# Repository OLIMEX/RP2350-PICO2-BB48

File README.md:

# RP2350-PICO2-BB48
Raspberry Pi RP2350 PICO2 board with all 48 ports exposed, PSRAM 8MB, Flash 16MB

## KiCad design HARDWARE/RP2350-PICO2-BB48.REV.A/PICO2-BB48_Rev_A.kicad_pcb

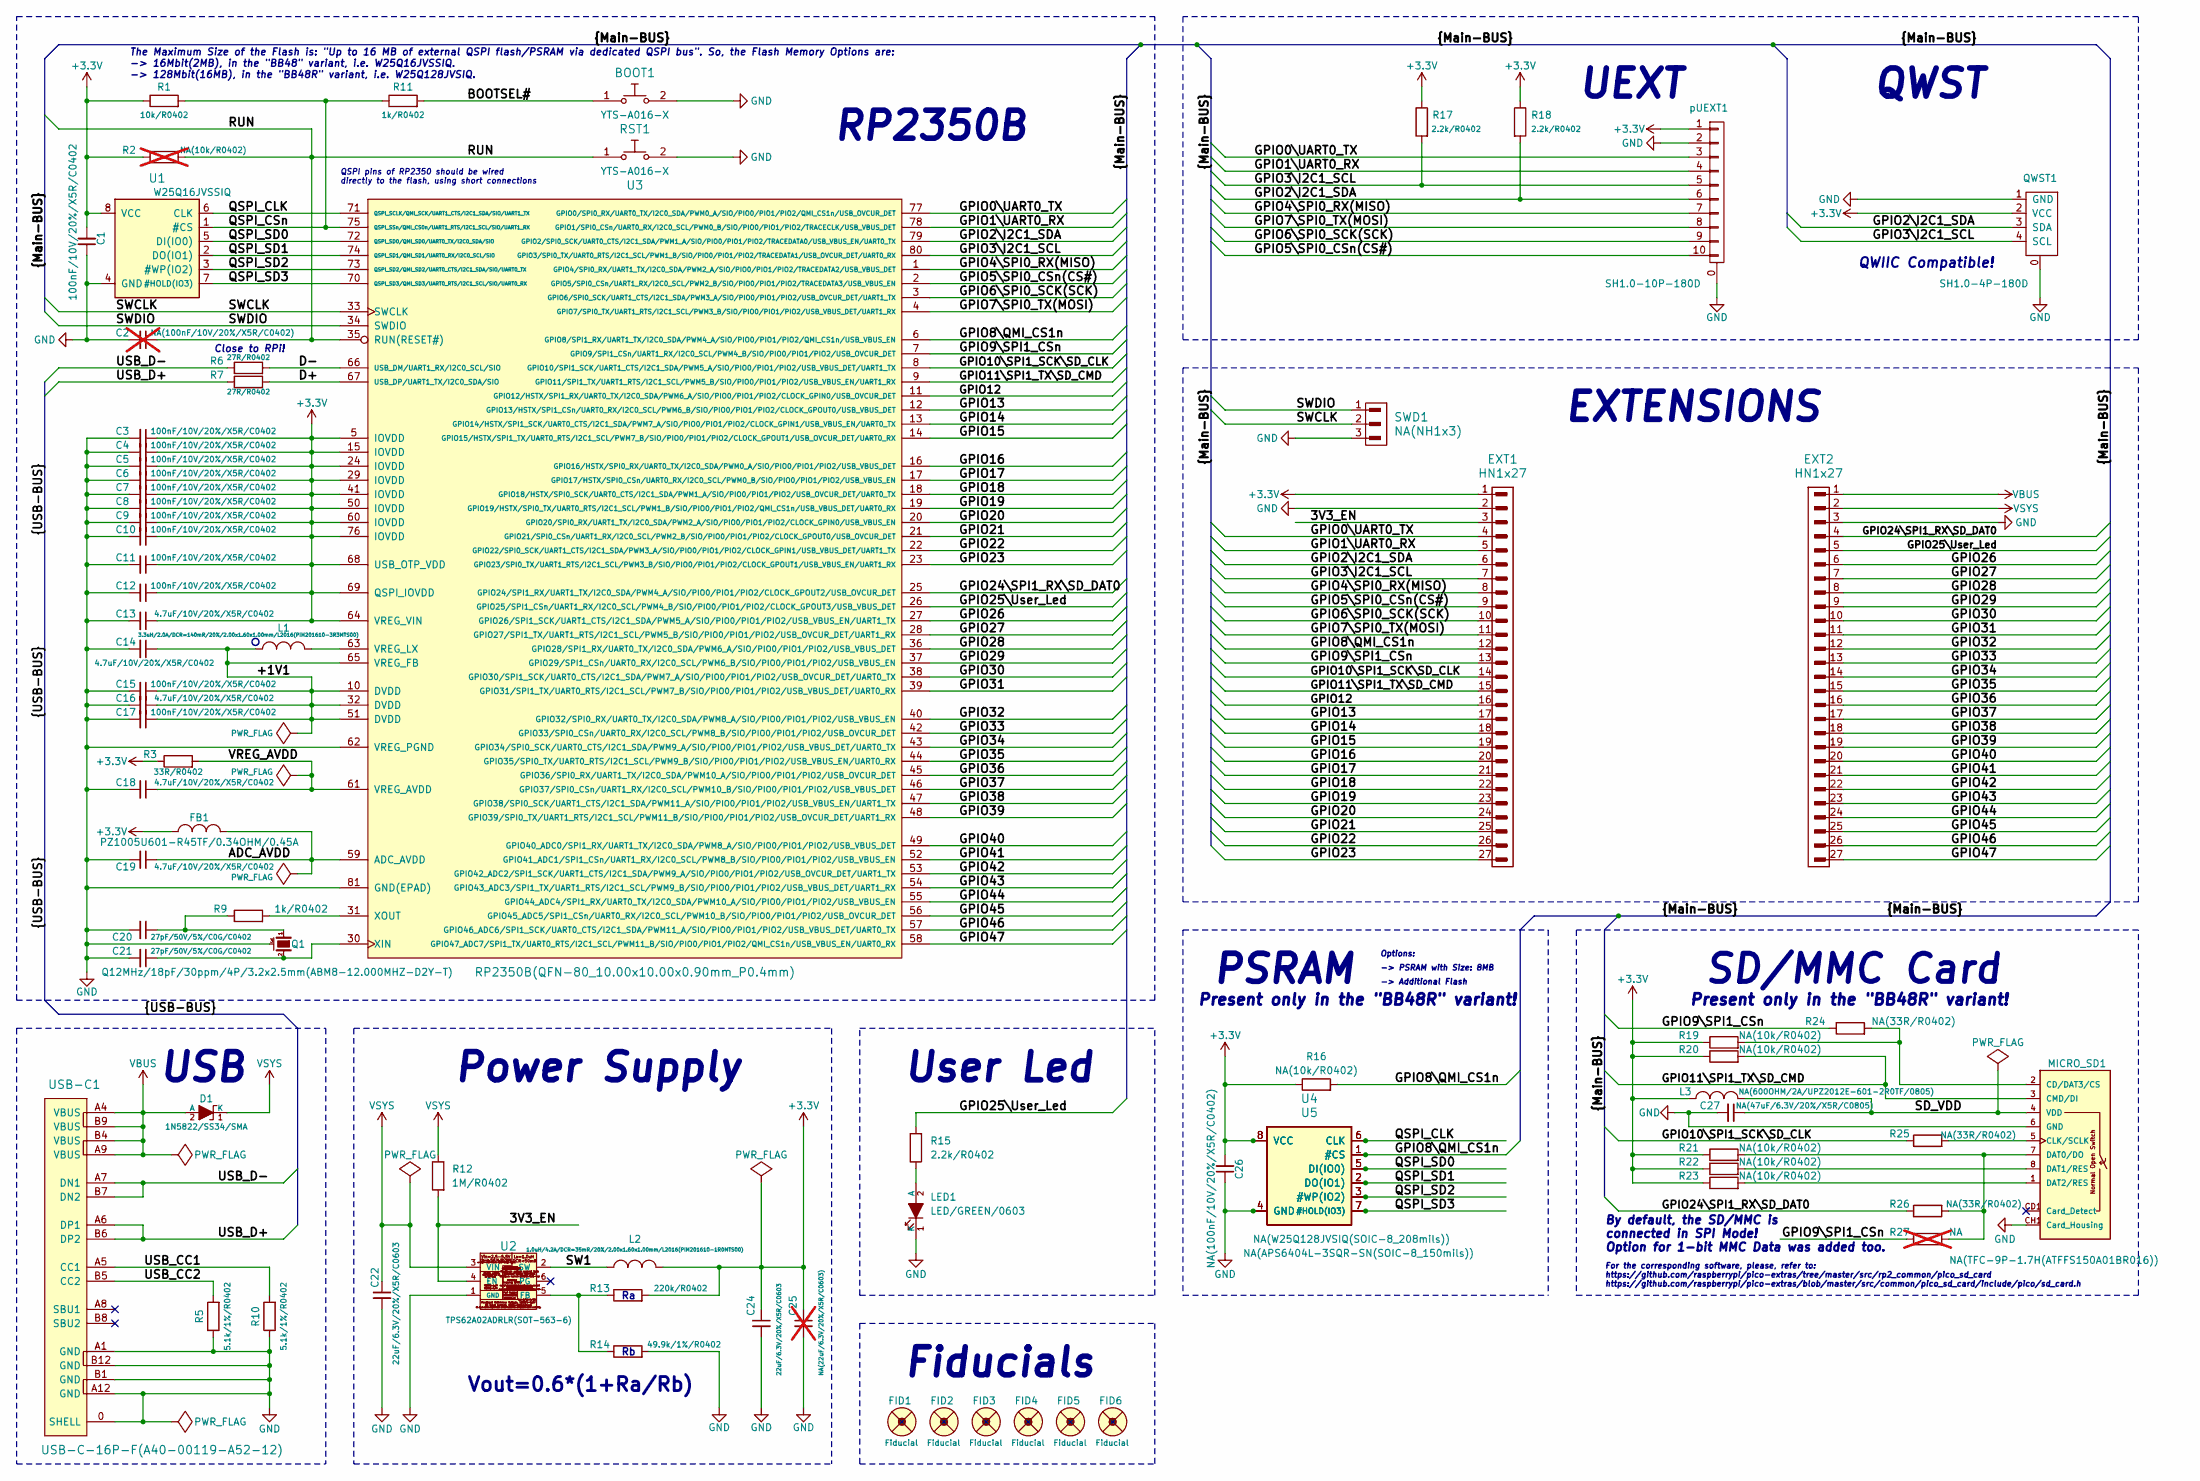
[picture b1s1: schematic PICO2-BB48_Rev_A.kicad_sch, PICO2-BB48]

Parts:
BOOT1: YTS-A016-X
C1, C3, C4, C5, C6, C7, C8, C9, C10, C11, C12, C15, C17: 100nF/10V/20%/X5R/C0402; C_0402_5MIL_DWS
C2: NA(100nF/10V/20%/X5R/C0402); C_0402_5MIL_DWS; not fitted
C13, C14, C16, C18, C19: 4.7uF/10V/20%/X5R/C0402; C_0402_5MIL_DWS
C20, C21: 27pF/50V/5%/C0G/C0402; C_0402_5MIL_DWS
C22, C24: 22uF/6.3V/20%/X5R/C0603; C_0603_5MIL_DWS
C25: NA(22uF/6.3V/20%/X5R/C0603); C_0603_5MIL_DWS; not fitted
C26: NA(100nF/10V/20%/X5R/C0402); C_0402_5MIL_DWS
C27: NA(47uF/6.3V/20%/X5R/C0805); C_0805_5MIL_DWS
D1: 1N5822/SS34/SMA; SMA-KA
EXT1, EXT2: HN1x27
FB1: PZ1005U601-R45TF/0.34OHM/0.45A; L_0402_5MIL_DWS
FID1, FID4: Fiducial; Fiducial1x3_Paste
FID2, FID3, FID5, FID6: Fiducial; Fiducial1x3
L1: 3.3uH/2.0A/DCR=140mR/20%/2.00x1.60x1.00mm/L2016(P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; L_2016_MM
L2: 1.0uH/4.2A/DCR=35mR/20%/2.00x1.60x1.00mm/L2016(PI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; L_2016_MM
L3: NA(600OHM/2A/UPZ2012E-601-2R0TF/0805); L_0805_5MIL_DWS
LED1: LED/GREEN/0603; LED_0603_KA
MICRO_SD1: NA(TFC-9P-1.7H(ATFFS150A01BR016)); uSD(TFC-9P-1.xH(ATFFS150A01BR016))
Q1: Q12MHz/18pF/30ppm/4P/3.2x2.5mm(ABM8-12.000MHZ-D2Y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; TSX-3.2x2.5mm_GND(3)
QWST1: SH1.0-4P-180D; BM04B-SRSS-TB
R1: 10k/R0402; R_0402_5MIL_DWS
R2: NA(10k/R0402); R_0402_5MIL_DWS; not fitted
R3: 33R/R0402; R_0402_5MIL_DWS
R5, R10: 5.1k/1%/R0402; R_0402_5MIL_DWS
R6, R7: 27R/R0402; R_0402_5MIL_DWS
R9, R11: 1k/R0402; R_0402_5MIL_DWS
R12: 1M/R0402; R_0402_5MIL_DWS
R13: 220k/R0402; R_0402_5MIL_DWS
R14: 49.9k/1%/R0402; R_0402_5MIL_DWS
R15, R17, R18: 2.2k/R0402; R_0402_5MIL_DWS
R16, R19, R20, R21, R22, R23: NA(10k/R0402); R_0402_5MIL_DWS
R24, R25, R26: NA(33R/R0402); R_0402_5MIL_DWS
R27: NA; R_0402_5MIL_DWS; not fitted
RST1: YTS-A016-X
SWD1: NA(NH1x3); HN1x3
U1: W25Q16JVSSIQ; SO-8_208mil
U2: TPS62A02ADRLR(SOT-563-6); SOT-563-6
U3: RP2350B(QFN-80_10.00x10.00x0.90mm_P0.4mm); QFN-80_10.00x10.00x0.90mm_P0.4mm
U4: NA(W25Q128JVSIQ(SOIC-8_208mils)); SO-8_208mil
U5: NA(APS6404L-3SQR-SN(SOIC-8_150mils)); SO-8
USB-C1: USB-C-16P-F(A40-00119-A52-12); USB2.0_TYPE-C(A40-00119-A52-12)_Paste
pUEXT1: SH1.0-10P-180D; BM10B-SRSS-TB

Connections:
+3.3V: C1.2, C3.1, C4.1, C5.1, C6.1, C7.1, C8.1, C9.1, C10.1, C11.1, C12.1, C13.1, C24.1, C25.1, C26.2, EXT1.1, FB1.1, L2.1, L3.1, QWST1.2 (VCC), R1.1, R2.1, R3.1, R13.2, R16.1, R17.1, R18.1, R19.1, R20.1, R21.1, R22.1, R23.1, U1.8 (VCC), U3.5 (IOVDD), U3.15 (IOVDD), U3.24 (IOVDD), U3.29 (IOVDD), U3.41 (IOVDD), U3.50 (IOVDD), U3.60 (IOVDD), U3.64 (VREG_VIN), U3.68 (USB_OTP_VDD), U3.69 (QSPI_IOVDD), U3.76 (IOVDD), U4.8 (VCC), U5.8 (VCC), pUEXT1.1
/3V3_EN: EXT1.3, R12.2, U2.4 (EN)
/+1V1: C14.1, C15.1, C16.1, C17.1, L1.1, U3.10 (DVDD), U3.32 (DVDD), U3.51 (DVDD), U3.65 (VREG_FB)
/ADC_AVDD: C19.1, FB1.2, U3.59 (ADC_AVDD)
/BOOTSEL#: BOOT1.1, R11.2
/D+: R7.2, U3.67 (USB_DP/UART1_TX/I2C0_SDA/SIO)
/D-: R6.2, U3.66 (USB_DM/UART1_RX/I2C0_SCL/SIO)
/GPIO0\UART0_TX: EXT1.4, U3.77 (GPIO0/SPI0_RX/UART0_TX/I2C0_SDA/PWM0_A/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), pUEXT1.3
/GPIO1\UART0_RX: EXT1.5, U3.78 (GPIO1/SPI0_CSn/UART0_RX/I2C0_SCL/PWM0_B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), pUEXT1.4
/GPIO2\I2C1_SDA: EXT1.6, QWST1.3 (SDA), R18.2, U3.79 (GPIO2/SPI0_SCK/UART0_CTS/I2C1_SDA/PWM1_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), pUEXT1.6
/GPIO3\I2C1_SCL: EXT1.7, QWST1.4 (SCL), R17.2, U3.80 (GPIO3/SPI0_TX/UART0_RTS/I2C1_SCL/PWM1_B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), pUEXT1.5
/GPIO4\SPI0_RX(MISO): EXT1.8, U3.1 (GPIO4/SPI0_RX/UART1_TX/I2C0_SDA/PWM2_A/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), pUEXT1.7
/GPIO5\SPI0_CSn(CS#): EXT1.9, U3.2 (GPIO5/SPI0_CSn/UART1_RX/I2C0_SCL/PWM2_B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), pUEXT1.10
/GPIO6\SPI0_SCK(SCK): EXT1.10, U3.3 (GPIO6/SPI0_SCK/UART1_CTS/I2C1_SDA/PWM3_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), pUEXT1.9
/GPIO7\SPI0_TX(MOSI): EXT1.11, U3.4 (GPIO7/SPI0_TX/UART1_RTS/I2C1_SCL/PWM3_B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), pUEXT1.8
/GPIO8\QMI_CS1n: EXT1.12, R16.2, U3.6 (GPIO8/SPI1_RX/UART1_TX/I2C0_SDA/PWM4_A/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), U4.1 (#CS), U5.1 (#CS)
/GPIO9\SPI1_CSn: EXT1.13, R24.1, R27.1, U3.7 (GPIO9/SPI1_CSn/UART1_RX/I2C0_SCL/PWM4_B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)
/GPIO10\SPI1_SCK\SD_CLK: EXT1.14, R25.1, U3.8 (GPIO10/SPI1_SCK/UART1_CTS/I2C1_SDA/PWM5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)
/GPIO11\SPI1_TX\SD_CMD: EXT1.15, MICRO_SD1.3 (CMD/DI), R20.2, U3.9 (GPIO11/SPI1_TX/UART1_RTS/I2C1_SCL/PWM5_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)
/GPIO12: EXT1.16, U3.11 (GPIO12/HSTX/SPI1_RX/UART0_TX/I2C0_SDA/P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)
/GPIO13: EXT1.17, U3.12 (GPIO13/HSTX/SPI1_CSn/UART0_RX/I2C0_SCL/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)
/GPIO14: EXT1.18, U3.13 (GPIO14/HSTX/SPI1_SCK/UART0_CTS/I2C1_SDA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)
/GPIO15: EXT1.19, U3.14 (GPIO15/HSTX/SPI1_TX/UART0_RTS/I2C1_SCL/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)
/GPIO16: EXT1.20, U3.16 (GPIO16/HSTX/SPI0_RX/UART0_TX/I2C0_SDA/P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)
/GPIO17: EXT1.21, U3.17 (GPIO17/HSTX/SPI0_CSn/UART0_RX/I2C0_SCL/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)
/GPIO18: EXT1.22, U3.18 (GPIO18/HSTX/SPI0_SCK/UART0_CTS/I2C1_SDA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)
/GPIO19: EXT1.23, U3.19 (GPIO19/HSTX/SPI0_TX/UART0_RTS/I2C1_SCL/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)
/GPIO20: EXT1.24, U3.20 (GPIO20/SPI0_RX/UART1_TX/I2C0_SDA/PWM2_A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)
/GPIO21: EXT1.25, U3.21 (GPIO21/SPI0_CSn/UART1_RX/I2C0_SCL/PWM2_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)
/GPIO22: EXT1.26, U3.22 (GPIO22/SPI0_SCK/UART1_CTS/I2C1_SDA/PWM3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)
/GPIO23: EXT1.27, U3.23 (GPIO23/SPI0_TX/UART1_RTS/I2C1_SCL/PWM3_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)
/GPIO24\SPI1_RX\SD_DAT0: EXT2.4, R26.1, U3.25 (GPIO24/SPI1_RX/UART1_TX/I2C0_SDA/PWM4_A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)
/GPIO25\User_Led: EXT2.5, R15.2, U3.26 (GPIO25/SPI1_CSn/UART1_RX/I2C0_SCL/PWM4_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)
/GPIO26: EXT2.6, U3.27 (GPIO26/SPI1_SCK/UART1_CTS/I2C1_SDA/PWM5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)
/GPIO27: EXT2.7, U3.28 (GPIO27/SPI1_TX/UART1_RTS/I2C1_SCL/PWM5_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)
/GPIO28: EXT2.8, U3.36 (GPIO28/SPI1_RX/UART0_TX/I2C0_SDA/PWM6_A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)
/GPIO29: EXT2.9, U3.37 (GPIO29/SPI1_CSn/UART0_RX/I2C0_SCL/PWM6_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)
/GPIO30: EXT2.10, U3.38 (GPIO30/SPI1_SCK/UART0_CTS/I2C1_SDA/PWM7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)
/GPIO31: EXT2.11, U3.39 (GPIO31/SPI1_TX/UART0_RTS/I2C1_SCL/PWM7_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)
/GPIO32: EXT2.12, U3.40 (GPIO32/SPI0_RX/UART0_TX/I2C0_SDA/PWM8_A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)
/GPIO33: EXT2.13, U3.42 (GPIO33/SPI0_CSn/UART0_RX/I2C0_SCL/PWM8_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)
/GPIO34: EXT2.14, U3.43 (GPIO34/SPI0_SCK/UART0_CTS/I2C1_SDA/PWM9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)
/GPIO35: EXT2.15, U3.44 (GPIO35/SPI0_TX/UART0_RTS/I2C1_SCL/PWM9_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)
/GPIO36: EXT2.16, U3.45 (GPIO36/SPI0_RX/UART1_TX/I2C0_SDA/PWM10_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)
/GPIO37: EXT2.17, U3.46 (GPIO37/SPI0_CSn/UART1_RX/I2C0_SCL/PWM10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)
/GPIO38: EXT2.18, U3.47 (GPIO38/SPI0_SCK/UART1_CTS/I2C1_SDA/PWM1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)
/GPIO39: EXT2.19, U3.48 (GPIO39/SPI0_TX/UART1_RTS/I2C1_SCL/PWM11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)
/GPIO40: EXT2.20, U3.49 (GPIO40_ADC0/SPI1_RX/UART1_TX/I2C0_SDA/P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)
/GPIO41: EXT2.21, U3.52 (GPIO41_ADC1/SPI1_CSn/UART1_RX/I2C0_SCL/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)
/GPIO42: EXT2.22, U3.53 (GPIO42_ADC2/SPI1_SCK/UART1_CTS/I2C1_SDA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)
/GPIO43: EXT2.23, U3.54 (GPIO43_ADC3/SPI1_TX/UART1_RTS/I2C1_SCL/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)
/GPIO44: EXT2.24, U3.55 (GPIO44_ADC4/SPI1_RX/UART0_TX/I2C0_SDA/P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)
/GPIO45: EXT2.25, U3.56 (GPIO45_ADC5/SPI1_CSn/UART0_RX/I2C0_SCL/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)
/GPIO46: EXT2.26, U3.57 (GPIO46_ADC6/SPI1_SCK/UART0_CTS/I2C1_SDA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)
/GPIO47: EXT2.27, U3.58 (GPIO47_ADC7/SPI1_TX/UART0_RTS/I2C1_SCL/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)
/QSPI_CLK: U1.6 (CLK), U3.71 (QSPI_SCLK/QMI_SCK/UART1_CTS/I2C1_SDA/SI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), U4.6 (CLK), U5.6 (CLK)
/QSPI_CSn: R1.2, R11.1, U1.1 (#CS), U3.75 (QSPI_SSn/QMI_CS0n/UART1_RTS/I2C1_SCL/SI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)
/QSPI_SD0: U1.5 (DI(IO0)), U3.72 (QSPI_SD0/QMI_SD0/UART0_TX/I2C0_SDA/SIO), U4.5 (DI(IO0)), U5.5 (DI(IO0))
/QSPI_SD1: U1.2 (DO(IO1)), U3.74 (QSPI_SD1/QMI_SD1/UART0_RX/I2C0_SCL/SIO), U4.2 (DO(IO1)), U5.2 (DO(IO1))
/QSPI_SD2: U1.3 (#WP(IO2)), U3.73 (QSPI_SD2/QMI_SD2/UART0_CTS/I2C1_SDA/SIO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), U4.3 (#WP(IO2)), U5.3 (#WP(IO2))
/QSPI_SD3: U1.7 (#HOLD(IO3)), U3.70 (QSPI_SD3/QMI_SD3/UART0_RTS/I2C1_SCL/SIO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), U4.7 (#HOLD(IO3)), U5.7 (#HOLD(IO3))
/RUN: C2.1, R2.2, RST1.1, U3.35 (RUN(RESET#))
/SD_VDD: C27.1, L3.2, MICRO_SD1.4 (VDD)
/SW1: L2.2, U2.2 (SW)
/SWCLK: SWD1.2, U3.33 (SWCLK)
/SWDIO: SWD1.1, U3.34 (SWDIO)
/USB_CC1: R10.2, USB-C1.A5 (CC1)
/USB_CC2: R5.2, USB-C1.B5 (CC2)
/USB_D+: R7.1, USB-C1.A6 (DP1), USB-C1.B6 (DP2)
/USB_D-: R6.1, USB-C1.A7 (DN1), USB-C1.B7 (DN2)
/VREG_AVDD: C18.1, R3.2, U3.61 (VREG_AVDD)
GND: BOOT1.2, C1.1, C2.2, C3.2, C4.2, C5.2, C6.2, C7.2, C8.2, C9.2, C10.2, C11.2, C12.2, C13.2, C14.2, C15.2, C16.2, C17.2, C18.2, C19.2, C20.2, C21.2, C22.2, C24.2, C25.2, C26.1, C27.2, EXT1.2, EXT2.3, LED1.1 (K), MICRO_SD1.6 (GND), MICRO_SD1.CH1 (Card_Housing), Q1.3 (case), QWST1.0, QWST1.1 (GND), R5.1, R10.1, R14.2, RST1.2, SWD1.3, U1.4 (GND), U2.1 (GND), U3.62 (VREG_PGND), U3.81 (GND(EPAD)), U4.4 (GND), U5.4 (GND), USB-C1.0 (SHELL), USB-C1.A1 (GND), USB-C1.A12 (GND), USB-C1.B1 (GND), USB-C1.B12 (GND), pUEXT1.0, pUEXT1.2
unnamed: C20.1, Q1.1, R9.1
unnamed: LED1.2 (A), R15.1
unnamed: MICRO_SD1.2 (CD/DAT3/CS), R19.2, R24.2
unnamed: MICRO_SD1.5 (CLK/SCLK), R25.2
unnamed: MICRO_SD1.7 (DAT0/DO), R21.2, R26.2, R27.2
unnamed: MICRO_SD1.8 (DAT1/RES), R22.2
unnamed: MICRO_SD1.1 (DAT2/RES), R23.2
unnamed: R13.1, R14.1, U2.5 (FB)
unnamed: L1.2, U3.63 (VREG_LX)
unnamed: C21.1, Q1.2, U3.30 (XIN)
unnamed: R9.2, U3.31 (XOUT)
VBUS: D1.2 (A), EXT2.1, USB-C1.A4 (VBUS), USB-C1.A9 (VBUS), USB-C1.B4 (VBUS), USB-C1.B9 (VBUS)
VSYS: C22.1, D1.1 (K), EXT2.2, R12.1, U2.3 (VIN)

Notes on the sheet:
Present only in the "BB48R" variant!
EXTENSIONS
QSPI pins of RP2350 should be wired directly to the flash, using short connections
-> PSRAM with Size: 8MB
By default, the SD/MMC is connected in SPI Mode! Option for 1-bit MMC Data was added too.
The Maximum Size of the Flash is: "Up to 16 MB of external QSPI flash/PSRAM via dedicated QSPI bus". So, the Flash Memory Options are: -> 16Mbit(2MB), in the "BB48" variant, i.e. W25Q16JVSSIQ. -> 128Mbit(16MB), in the "BB48R" variant, i.e. W25Q128JVSIQ.
SD/MMC Card
QWST
USB
User Led
For the corresponding software, please, refer to: https://github.com/raspberrypi/pico-extras/tree/master/src/rp2_common/pico_sd_card https://github.com/raspberrypi/pico-extras/blob/master/src/common/pico_sd_card/include/pico/sd_card.h
Options:
-> Additional Flash
QWIIC Compatible!
Close to RPi!
RP2350B
Vout=0.6*(1+Ra/Rb)
Power Supply
PSRAM
Fiducials
UEXT

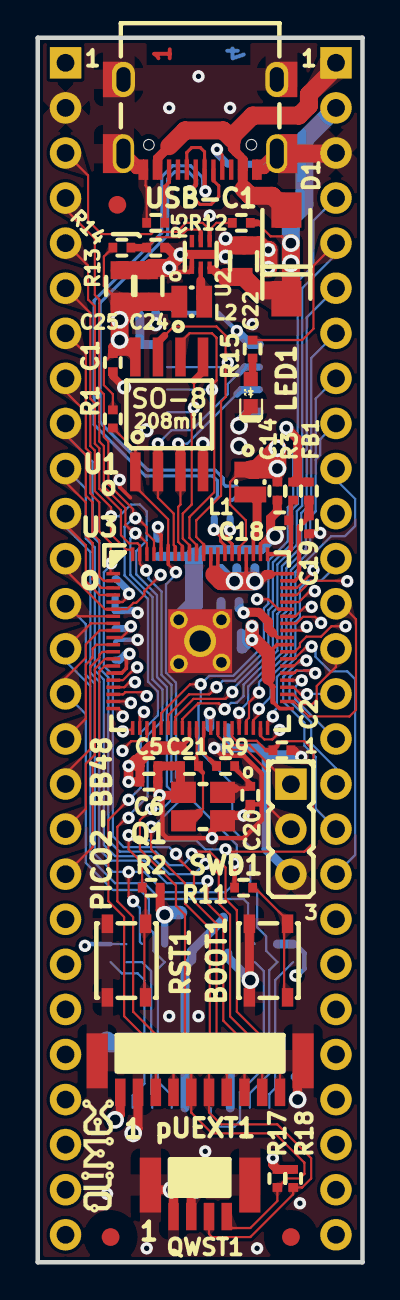
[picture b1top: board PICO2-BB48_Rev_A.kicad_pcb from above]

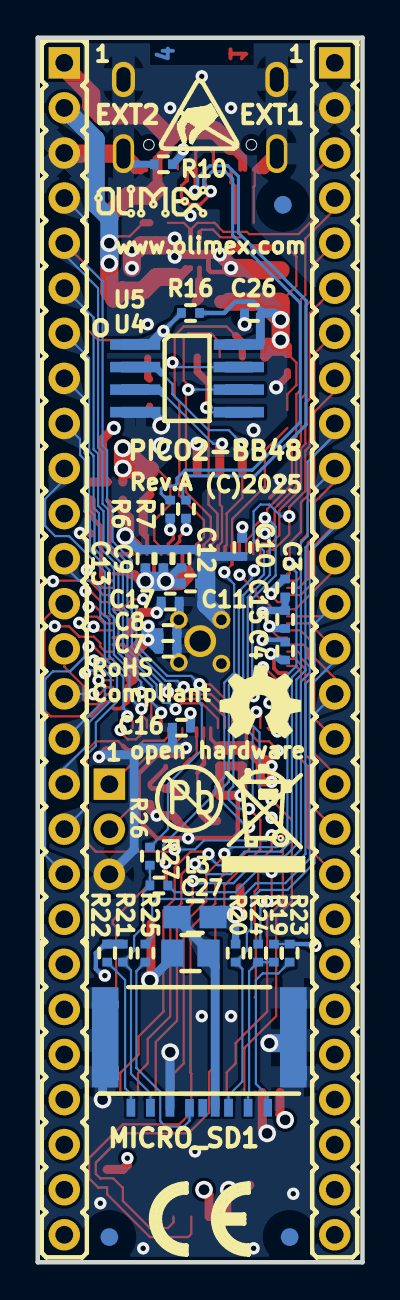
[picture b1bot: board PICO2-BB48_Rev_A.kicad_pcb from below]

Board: 4 copper layers, 18.3 x 69.0 mm, 85 parts (42 on the bottom side), 85 nets.

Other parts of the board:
Logo_OLIMEX_80, Logo_OLIMEX_80-Bot: Logo_OLIMEX_80
Sign_Antistatic_Small: Sign_Antistatic; Sign_Antistatic_4.5mmX2.8mm
Sign_CE: CE_Sign
Sign_OSHW_7.3x6.0mm: Sign_OSHW_7.3x6.0mm; Sign_OSHW_7.3x6.0mmn
Sign_PB-Free: Sign_PB-Free
Sign_RecycleBin_1: Sign_RecycleBin_1

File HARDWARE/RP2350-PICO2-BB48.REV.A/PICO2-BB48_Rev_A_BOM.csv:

"Id";"Designator";"Footprint";"Quantity";"Designation";"Supplier and ref";
1;"FID1,FID4";"Fiducial1x3_Paste";2;"Fiducial";;;
2;"LED1";"LED_0603_KA";1;"LED/GREEN/0603";;;
3;"FID3,FID2,FID6,FID5";"Fiducial1x3";4;"Fiducial";;;
4;"D1";"SMA-KA";1;"1N5822/SS34/SMA";;;
5;"R18,R17,R15";"R_0402_5MIL_DWS";3;"2.2k/R0402";;;
6;"RST1,BOOT1";"YTS-A016-X";2;"YTS-A016-X";;;
7;"R5,R10";"R_0402_5MIL_DWS";2;"5.1k/1%/R0402";;;
8;"R12";"R_0402_5MIL_DWS";1;"1M/R0402";;;
9;"pUEXT1";"BM10B-SRSS-TB";1;"SH1.0-10P-180D";;;
10;"USB-C1";"USB2.0_TYPE-C(A40-00119-A52-12)_Paste";1;"USB-C-16P-F(A40-00119-A52-12)";;;
11;"R13";"R_0402_5MIL_DWS";1;"220k/R0402";;;
12;"C14,C18,C19,C16,C13";"C_0402_5MIL_DWS";5;"4.7uF/10V/20%/X5R/C0402";;;
13;"SWD1";"HN1x3";1;"NA(NH1x3)";;;
14;"L1";"L_2016_MM";1;"3.3uH/2.0A/DCR=140mR/20%/2.00x1.60x1.00mm/L2016(PIM201610-3R3MTS00)";;;
15;"R2,R20,R16,R23,R21,R22,R19";"R_0402_5MIL_DWS";7;"NA(10k/R0402)";;;
16;"Q1";"TSX-3.2x2.5mm_GND(3)";1;"Q12MHz/18pF/30ppm/4P/3.2x2.5mm(ABM8-12.000MHZ-D2Y-T)";;;
17;"C21,C20";"C_0402_5MIL_DWS";2;"27pF/50V/5%/C0G/C0402";;;
18;"FB1";"L_0402_5MIL_DWS";1;"PZ1005U601-R45TF/0.34OHM/0.45A";;;
19;"C22,C24";"C_0603_5MIL_DWS";2;"22uF/6.3V/20%/X5R/C0603";;;
20;"C2,C26";"C_0402_5MIL_DWS";2;"NA(100nF/10V/20%/X5R/C0402)";;;
21;"U3";"QFN-80_10.00x10.00x0.90mm_P0.4mm";1;"RP2350B(QFN-80_10.00x10.00x0.90mm_P0.4mm)";;;
22;"L2";"L_2016_MM";1;"1.0uH/4.2A/DCR=35mR/20%/2.00x1.60x1.00mm/L2016(PIM201610-1R0MTS00)";;;
23;"U2";"SOT-563-6";1;"TPS62A02ADRLR(SOT-563-6)";;;
24;"R3";"R_0402_5MIL_DWS";1;"33R/R0402";;;
25;"R11,R9";"R_0402_5MIL_DWS";2;"1k/R0402";;;
26;"R1";"R_0402_5MIL_DWS";1;"10k/R0402";;;
27;"C1,C6,C5,C10,C4,C17,C9,C11,C3,C8,C12,C7,C15";"C_0402_5MIL_DWS";13;"100nF/10V/20%/X5R/C0402";;;
28;"U1";"SO-8_208mil";1;"W25Q16JVSSIQ";;;
29;"C25";"C_0603_5MIL_DWS";1;"NA(22uF/6.3V/20%/X5R/C0603)";;;
30;"R14";"R_0402_5MIL_DWS";1;"49.9k/1%/R0402";;;
31;"QWST1";"BM04B-SRSS-TB";1;"SH1.0-4P-180D";;;
32;"R7,R6";"R_0402_5MIL_DWS";2;"27R/R0402";;;
33;"U4";"SO-8_208mil";1;"NA(W25Q128JVSIQ(SOIC-8_208mils))";;;
34;"U5";"SO-8";1;"NA(APS6404L-3SQR-SN(SOIC-8_150mils))";;;
35;"R25,R24,R26";"R_0402_5MIL_DWS";3;"NA(33R/R0402)";;;
36;"EXT2,EXT1";"HN1x27";2;"HN1x27";;;
37;"L3";"L_0805_5MIL_DWS";1;"NA(600OHM/2A/UPZ2012E-601-2R0TF/0805)";;;
38;"R27";"R_0402_5MIL_DWS";1;"NA";;;
39;"C27";"C_0805_5MIL_DWS";1;"NA(47uF/6.3V/20%/X5R/C0805)";;;
40;"MICRO_SD1";"uSD(TFC-9P-1.xH(ATFFS150A01BR016))";1;"NA(TFC-9P-1.7H(ATFFS150A01BR016))";;;

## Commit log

2025-09-22 initial upload
2025-09-22 add user manual

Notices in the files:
HARDWARE/RP2350-PICO2-BB48.REV.A/PICO2-BB48_Rev_A.kicad_pcb:
(C)2025
